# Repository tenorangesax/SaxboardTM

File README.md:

# Saxboard
A custom personalized devboard for me, more on the teaching side for me to understand how the raspberry pi pico boards work and how to do a little basic SMD soldering.

**[WORKING VIDEO DEMO!!](https://youtu.be/bMa3YCjVTW8)**

**Heres the finished product!!!!!!**

Schematic:

PCB:

BOM:
[Saxboard - Saxboard.csv.csv](https://github.com/user-attachments/files/26161219/Saxboard.-.Saxboard.csv.csv)

[Uploading JOURNAL (D<!--
  This journal is auto generated by Stasis.
-->

# 4/25/2026 7 PM - Soldering + testing and works!!

_Time spent: 3.5h_

The buttons arrived, and I got to work soldering!

I had to watch some tutorials on how to SMD solder, and it was hard, but I used my phone to zoom in on the board and got good focus on it to solder.

After soldering the mini 
LED and turtle button, I plugged it in, and it worked! I verifed the button was working because I put it into boot mode.

I ran some test code on it, and it is functional!!!

I tried a lot using Aurdino IDE to make the LED work, then Thonny, but I couldn't work the onboard or external LEDs. 

also while ordering from last few journals i saved money and cut costs a lot, i saved like $50 dollars

also updated github PICS and README to the final pictures too, and made a gif slideshow for showing off the stuff

Here are the pictures:

# 4/22/2026 2 AM - Arrival! (+ testing...)

_Time spent: 1.5h_

The package came today!!!! And it actually works!!!!
I attached some pictures below.

But I'm still waiting on my buttons to come so I can SMD solder them onto the board since the button is required to boot the board so I can program it. It is being read and working though!

I'll update on Friday when I get the button and solder. 

# 4/5/2026 3 PM - Even more reordering

_Time spent: 1h_

So there was errors with the specific footprints for C14 and C13, and i backtracked all the way and apparently the tutorial used the wrong footprint, so I had to redo the files and reroute a bit. I also changed C15 and C16 to 33pF instead of 15 because the tutorial never mentioned it but had it in their schematics and its footprints and materials BOM. I had to reassign everything on the JLCPCB ordering page and redo the order,

# 4/4/2026 3 PM - Ordered from JLCPCB

_Time spent: 1.75h_

There was a whole process on ordering it since there was issues with the BOM, but after a lot of searching and asking for help in slack, I realised that the two extra components I added were forcing it to do standard PCBA, in turn, rasing the price to not allow it to do global direct shipping. ($135 -->$45!!)

I also had to redo a part after submitting for review in JLCPCB because of a shortage.

I also ordered the amazon pin headers, I found out after asking some people that you could just split big pin headers into little ones instead of ordering small pin headers.

# 3/21/2026 7 PM - GIT repo, final touches, JCLPCB, and the day my sanity flew away

_Time spent: 3.75h_

I finished the github repo (you can click on the link [https://github.com/tenorangesax/SaxboardTM](url)

i finished the final touches to the pcb, did a lot of research and digging for all the errors i had on jlcpcb for importing the files, and wrapped it all up.

heres just some picture dump, everythings better on  the repo, you should go there instead

***NOTE: THE TRUE REAL BOM IS IN THE GITHUB, THERE WAS ERRORS IMPORTING IT HERE. I NEED J2,J3, and J4, THE PINS TO SOLDER.***

# 3/21/2026 3 PM - PCB He-double hockey sticks

_Time spent: 5.75h_

i didn't sleep at all and finished everything for the pcb

i had to reroute everything and do it like 2 or 3 times till i found an okay spot

here are the pics of some versions

i previously had all the capacitors next to the chip and it made everything difficult

and then there was like 70+ errors when i did the ground pool and had to go through each one.

# 3/19/2026 2 PM - PCB wiring

_Time spent: 0.6333333333333333h_

today i did some horrible pcb wiring, and i think i need to probably redo everything next time

oh well

heres the stuffs and timelapse

# 3/18/2026 3 PM - PCB Design

_Time spent: 2h_

i designed the pcb,
figured out the problem for the LED is not that big and can *technically* work on online forms and whatnot

i'm 99% sure everything on this is wrong

oh well

heres a failed timelapse (my computer was bugging out)

# 3/18/2026 1 AM - LED "addition"

_Time spent: 3.833333333333333h_

so today from last post i've wanted to add an led to signal different stuff like oh this is on or something embbed in the board.

it was the hardest thing in this project (to date)

i had to research about what leds support what currents, what options i should use, ext. 

i didn't finish it yet, and i'm pretty sure its wrong but heres the stuff.

i'll change it next post maybe bc I asked in slack and dm'd some people to ask

i was experimenting to see if it worked or not with some spare stuff i had and blew up some stuff by accident

the basic problem i had was that the DIN is supposed to be on 37 (GPIO25 on the chip) so i could control color and 3v3 for VDD to be on constantly as a side effect, but I think I have to put VDD on the chip and sacrifice a pin on the rails to control color.

# 3/16/2026 8 PM - Schematic + Errorfixing + Footprint assignments + Research

_Time spent: 5.616666666666667h_

Today i started my first project for Stasis.
I was orignally planning to do the spotify player, but  i decided to do the devboard instead cause it looked cooler

there was a lot of errors and stuff i forgot when cleaning up, and especially the crystal issue

i looked it up and did some searching, apparently for kicad, they had an update causing the crystal to have 3 pins instead of four, but its fine since the 4th is just another ground like the second pin.

i attached images of the jlcpcb actual crystal, my schematics, and the footprint assignments

i might add an led and maybe a resistor would be a good idea.

EVBOARD).md…]()

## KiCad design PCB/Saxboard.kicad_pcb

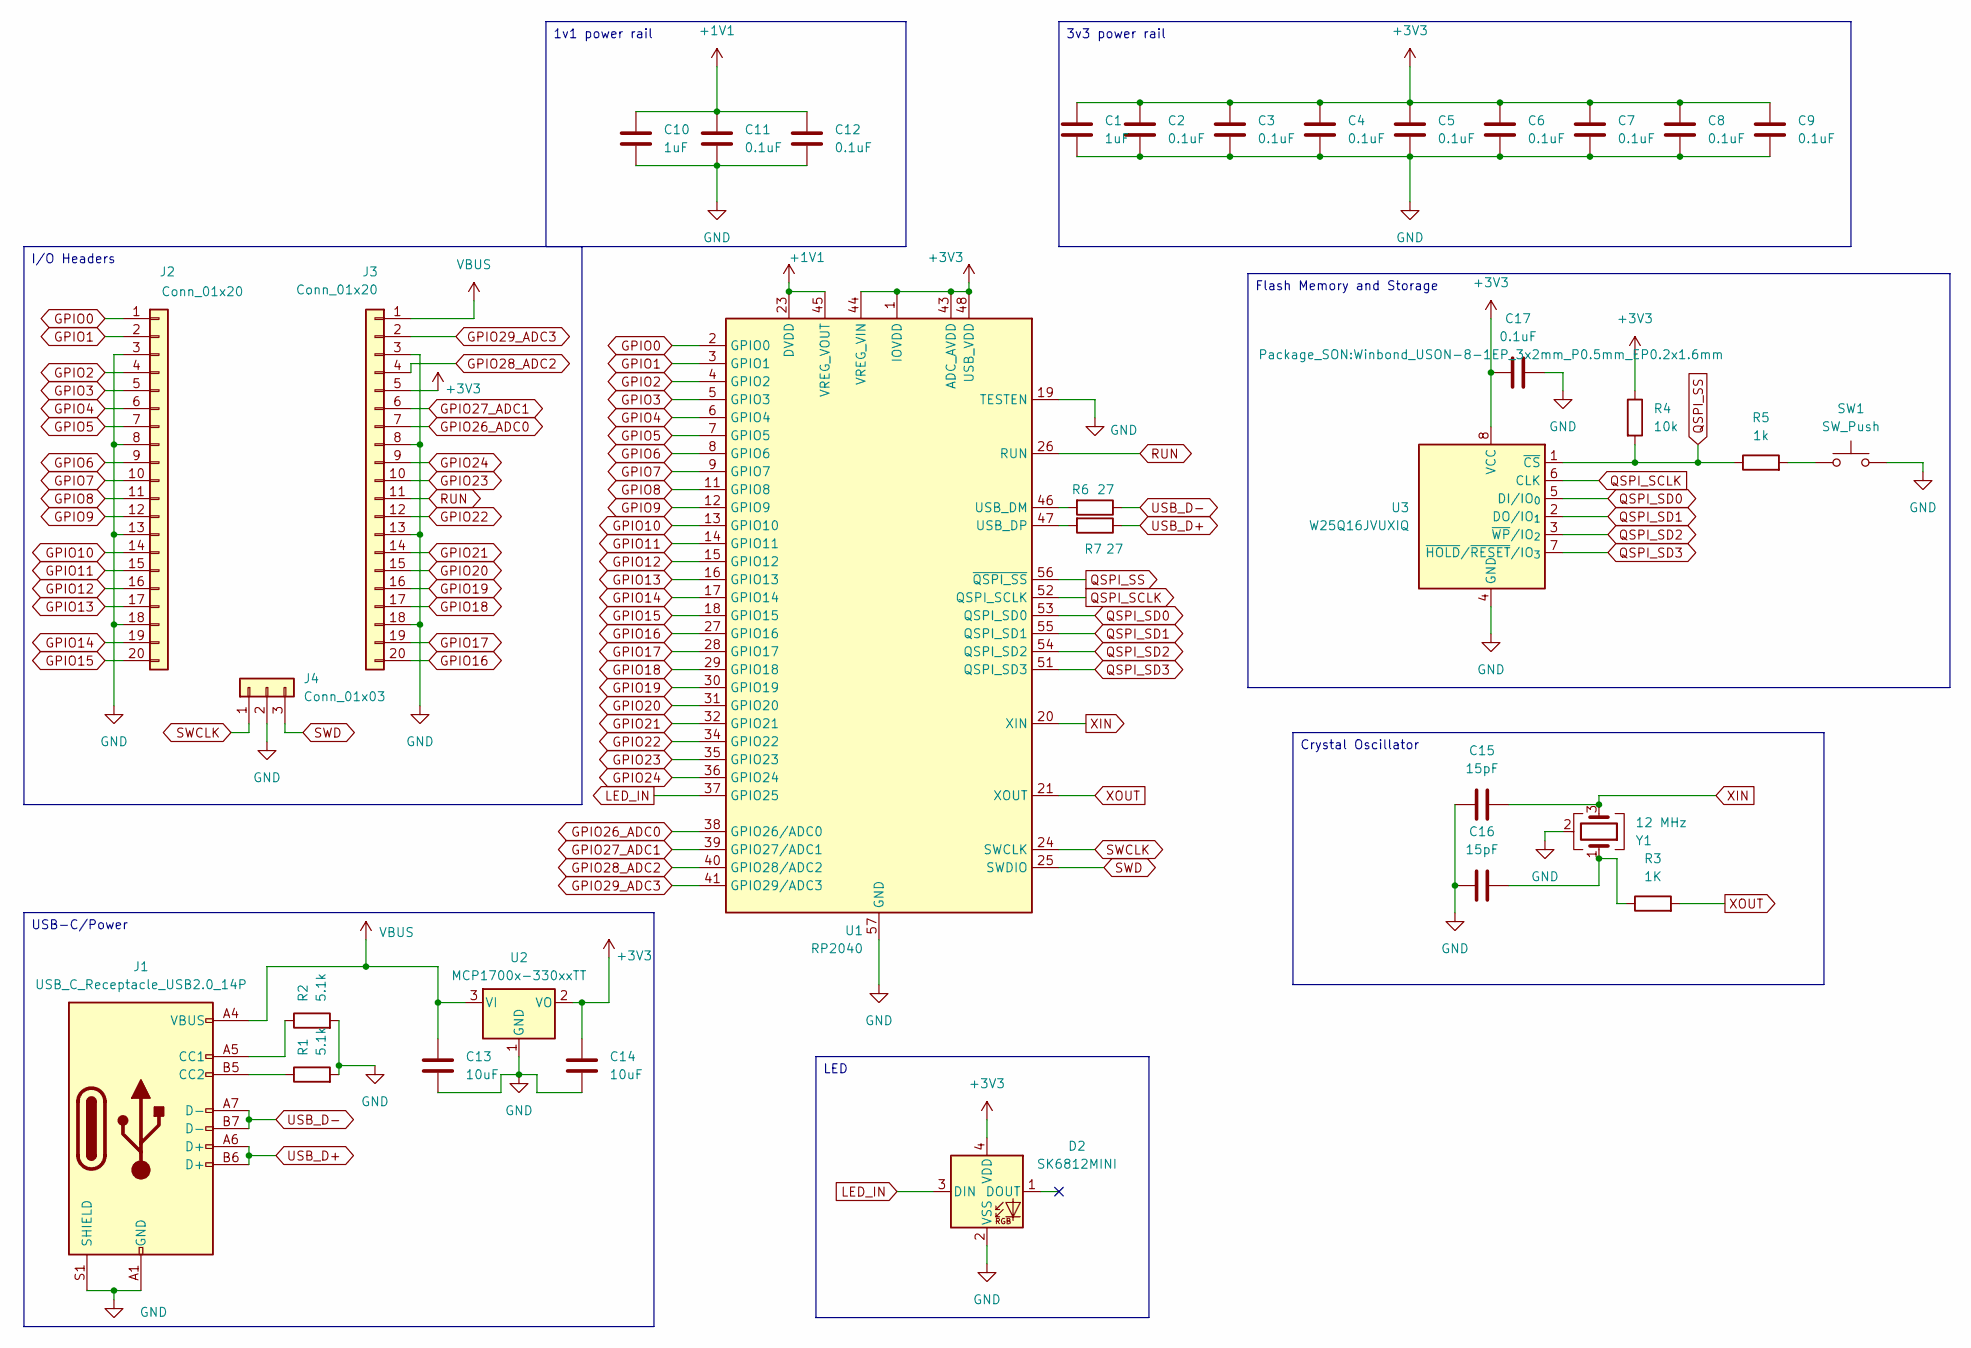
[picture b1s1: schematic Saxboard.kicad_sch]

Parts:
C1, C10: 1uF; C_0402_1005Metric
C2, C3, C4, C5, C6, C7, C8, C9, C11, C12, C17: 0.1uF; C_0402_1005Metric
C13, C14: 10uF; C_0402_1005Metric
C15, C16: 15pF; C_0402_1005Metric
D2: SK6812MINI; LED_SK6812MINI_PLCC4_3.5x3.5mm_P1.75mm
J1: USB_C_Receptacle_USB2.0_14P; USB_C_Receptacle_HRO_TYPE-C-31-M-12
J2, J3: Conn_01x20; PinHeader_1x20_P2.54mm_Vertical
J4: Conn_01x03; PinHeader_1x03_P2.54mm_Vertical
R1, R2: 5.1k; R_0402_1005Metric
R3: 1K; R_0402_1005Metric
R4: 10k; R_0402_1005Metric
R5: 1k; R_0402_1005Metric
R6, R7: 27; R_0402_1005Metric
SW1: SW_Push; SW_Push_SPST_NO_Alps_SKRK
U1: RP2040; QFN-56-1EP_7x7mm_P0.4mm_EP3.2x3.2mm
U2: MCP1700x-330xxTT; SOT-23
U3: W25Q16JVUXIQ; Winbond_USON-8-1EP_3x2mm_P0.5mm_EP0.2x1.6mm
Y1: 12 MHz; Crystal_SMD_3225-4Pin_3.2x2.5mm

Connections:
+1V1: C10.1, C11.1, C12.1, U1.23 (DVDD), U1.45 (VREG_VOUT), U1.50 (DVDD)
+3V3: C1.1, C2.1, C3.1, C4.1, C5.1, C6.1, C7.1, C8.1, C9.1, C14.1, C17.1, D2.4 (VDD), J3.5, R4.1, U1.1 (IOVDD), U1.10 (IOVDD), U1.22 (IOVDD), U1.33 (IOVDD), U1.42 (IOVDD), U1.43 (ADC_AVDD), U1.44 (VREG_VIN), U1.48 (USB_VDD), U1.49 (IOVDD), U2.2 (VO), U3.8 (VCC)
GND: C1.2, C2.2, C3.2, C4.2, C5.2, C6.2, C7.2, C8.2, C9.2, C10.2, C11.2, C12.2, C13.2, C14.2, C15.1, C16.1, C17.2, D2.2 (VSS), J1.A1 (GND), J1.A12 (GND), J1.B1 (GND), J1.B12 (GND), J1.S1 (SHIELD), J2.3, J2.8, J2.13, J2.18, J3.3, J3.8, J3.13, J3.18, J4.2, R1.2, R2.2, SW1.2, U1.19 (TESTEN), U1.57 (GND), U2.1 (GND), U3.4 (GND), Y1.2 (G), Y1.4 (G)
GPIO0: J2.1, U1.2 (GPIO0)
GPIO1: J2.2, U1.3 (GPIO1)
GPIO2: J2.4, U1.4 (GPIO2)
GPIO3: J2.5, U1.5 (GPIO3)
GPIO4: J2.6, U1.6 (GPIO4)
GPIO5: J2.7, U1.7 (GPIO5)
GPIO6: J2.9, U1.8 (GPIO6)
GPIO7: J2.10, U1.9 (GPIO7)
GPIO8: J2.11, U1.11 (GPIO8)
GPIO9: J2.12, U1.12 (GPIO9)
GPIO10: J2.14, U1.13 (GPIO10)
GPIO11: J2.15, U1.14 (GPIO11)
GPIO12: J2.16, U1.15 (GPIO12)
GPIO13: J2.17, U1.16 (GPIO13)
GPIO14: J2.19, U1.17 (GPIO14)
GPIO15: J2.20, U1.18 (GPIO15)
GPIO16: J3.20, U1.27 (GPIO16)
GPIO17: J3.19, U1.28 (GPIO17)
GPIO18: J3.17, U1.29 (GPIO18)
GPIO19: J3.16, U1.30 (GPIO19)
GPIO20: J3.15, U1.31 (GPIO20)
GPIO21: J3.14, U1.32 (GPIO21)
GPIO22: J3.12, U1.34 (GPIO22)
GPIO23: J3.10, U1.35 (GPIO23)
GPIO24: J3.9, U1.36 (GPIO24)
GPIO26_ADC0: J3.7, U1.38 (GPIO26/ADC0)
GPIO27_ADC1: J3.6, U1.39 (GPIO27/ADC1)
GPIO28_ADC2: J3.4, U1.40 (GPIO28/ADC2)
GPIO29_ADC3: J3.2, U1.41 (GPIO29/ADC3)
LED_IN: D2.3 (DIN), U1.37 (GPIO25)
unnamed: C16.2, R3.1, Y1.1
unnamed: J1.A5 (CC1), R2.1
unnamed: J1.B5 (CC2), R1.1
unnamed: R5.2, SW1.1
unnamed: R6.2, U1.46 (USB_DM)
unnamed: R7.2, U1.47 (USB_DP)
QSPI_SCLK: U1.52 (QSPI_SCLK), U3.6 (CLK)
QSPI_SD0: U1.53 (QSPI_SD0), U3.5 (DI/IO_{0})
QSPI_SD1: U1.55 (QSPI_SD1), U3.2 (DO/IO_{1})
QSPI_SD2: U1.54 (QSPI_SD2), U3.3 (~WP/IO_{2})
QSPI_SD3: U1.51 (QSPI_SD3), U3.7 (~HOLD/~RESET/IO_{3})
QSPI_SS: R4.2, R5.1, U1.56 (~QSPI_SS), U3.1 (~CS)
RUN: J3.11, U1.26 (RUN)
SWCLK: J4.1, U1.24 (SWCLK)
SWD: J4.3, U1.25 (SWDIO)
USB_D+: J1.A6 (D+), J1.B6 (D+), R7.1
USB_D-: J1.A7 (D-), J1.B7 (D-), R6.1
VBUS: C13.1, J1.A4 (VBUS), J1.A9 (VBUS), J1.B4 (VBUS), J1.B9 (VBUS), J3.1, U2.3 (VI)
XIN: C15.2, U1.20 (XIN), Y1.3
XOUT: R3.2, U1.21 (XOUT)

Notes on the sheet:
3v3 power rail
Crystal Oscillator
USB-C/Power
LED
1v1 power rail
Flash Memory and Storage
I/O Headers

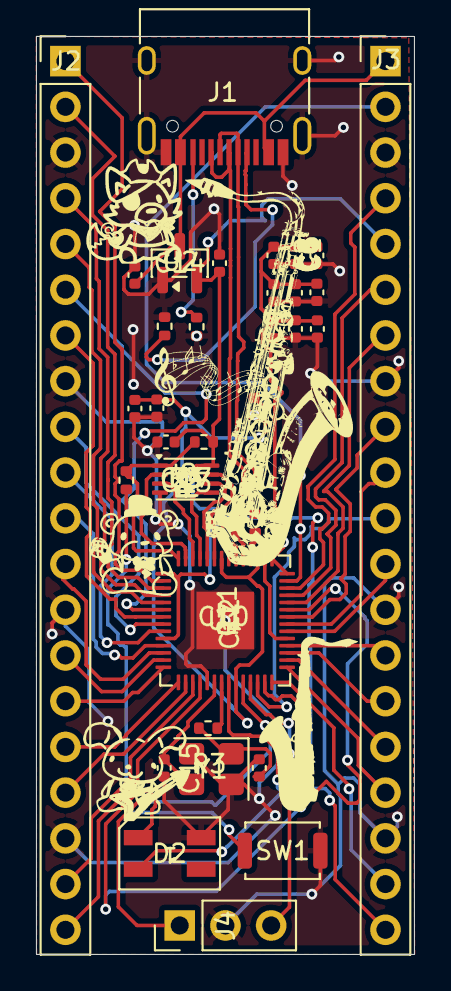
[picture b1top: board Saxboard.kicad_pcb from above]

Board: 2 copper layers, 21.0 x 51.0 mm, 34 parts (0 on the bottom side), 53 nets.

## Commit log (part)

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2026-03-21 Enhance README with project details and images
    Added images and detailed information about the Saxboard project, including schematic, PCB, BOM, and a picture dump.
2026-03-21 Enhance README formatting and add BOM images
    Updated formatting for emphasis and added images to the BOM section.
2026-03-21 Update README to remove image and refine text
    Removed image from README and updated description.
2026-03-21 Create dgf
2026-03-21 Create sdf
2026-03-21 Create fsd
2026-03-21 Create fds
2026-03-21 Create sfd
2026-03-21 Create dfsdfs
2026-03-21 Create fdsdfsfsd
2026-03-21 Create sf
2026-03-21 Create lhk
